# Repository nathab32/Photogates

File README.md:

# Photogate

[Video Demo](https://www.youtube.com/watch?v=dZhynI2hOx8)

## Description

Photogates allow precise, automatic timing of objects moving between two points. The photogates trigger automatically when a laser beam is interrupted, providing much faster response times than a human ever could with a stopwatch.

This specific project was inspired by my Science Olympiad team's lack of a photogate for the timing events. Commonly available solutions online cost at least $50, with high resolution ones costing hundreds of dollars. This design seeks to lower the barrier to precise timing by using commonly available parts and 3D printed materials for a cost-effective design. The design is fully open source to allow others to replicate and improve on it.

## Features

- Based on the Arduino UNO R3
- Swappable lasers and phototransistors
- Lasers and phototransistors mount to standard lab stands
- Displays last 3 recorded times
- Adjustable sensitivity
- Fully THT design
- Easy assembly

## Basic Usage

1. Position the two lasers perpendicular to the direction of travel at your specified distance.

2. Position the two phototransistors directly across from the two lasers. Each laser should hit straight onto a phototransistor.

3. Plug the lasers into the right side of the main module, and the phototransistors into the left side. The polarities are indicated on the silkscreen: a `+` for the lasers, and a `-` for the phototransistors.

4. When the module first powers on, calibration of the phototransistors will occur. The laser beams should be shining onto the phototransistors when this first occurs.

5. After calibration, make sure that the phototransistors are functioning by each beam independently. One of the interruptions should start the timing, indicated by `Timing...` on the LCD. The other interruption should stop the timing.
   - This is a good time to check the order of the phototransistors. If the order is incorrect, then simply plug the phototransistor in the top slot into the bottom slot and vice versa.

6. If everything has been executed correctly, then your photogate should be ready for timing! If you need to recalibrate at any point, simply press `R` again.

## Assembly

### 3D Printing

All 3D printing related files are included in the [`3D_Printing`](3D_Printing) directory. This includes the original `.f3d`, `.step`, and `.3mf` files.

If you don't use the `.3mf` file to slice, below are the parameters that I used.

|Parameter|Value|
|---------|-----|
|Material|PLA|
|Layer Height|0.2mm|
|Nozzle|0.4mm|
|Infill|<20%|

The biggest issue I had was with printing the lettering due to some elephant's foot, but if you have a multicolor printer then this won't be an issue. Otherwise, you may need to play around with the letter offsets and/or printer settings to get the letters to fit. The lettering is also entirely visual, so you can skip it if you want.

### Lasers

1. Cut and strip the 2 strand wire to the necessary length.

2. Cut heat shrink to the necessary length. I used heat shrink with a diameter that allows it to grab onto the laser diode's PCB when flattened so some strain relief is provided to the wire.

3. Solder female headers to one end of the wire.

4. Remove the presoldered wire from the laser diode, taking note of which side of the resistor the negative wire was attached to.

5. Slip the heat shrink onto the 2 strand wire.

6. Solder the 2 strand wire to the laser diode. The negative wire should bypass the included resistor by soldering to the side that the original wire wasn't connected to. Otherwise, the current source circuit may not be able to drive the laser.
    - A multimeter in the diode mode can check which side of the resistor to solder to. The side of the resistor with a lower voltage reading bypasses the resistor.

7. Test the connection by plugging the headers onto the laser pins on the shield and powering it on.

8. If laser powers on, then use the heat shrink over the flat portion of the laser's PCB. Don't slide it over the metal cylindrical section, otherwise the laser won't fit into the 3D printed mount.

9. Slide the laser diode into the 3D print, and use a M3x10 set screw to hold it in place.

10. Place the nut into the 3D print, and screw the eye bolt in. You can optionally glue the nut in place, but I chose not to just so I can remove it later if necessary.

The finshed result should look something like this:

### Phototransistors

1. Score and cut a 1x6 section of copper plated perfboard. If your perfboard has one continous copper side, then remove a small line of copper the middle of the board, leaving connections from holes 1-3 and holes 4-6.

2. Drill the first and last holes in the perfboard with a 7/64" drill bit to allow a M2 screw through.

3. Cut and strip the 2 strand wire to the necessary length.

4. Solder female headers to one end of the wire.

5. Bend the phototransistor leads towards the flat side of the package approximately 2.5mm from the bottom of the package. The phototransistor should be able to sit inside of the recession in the 3D print and the leads should stick through the 3rd and 4th holes of the perfboard.

6. With the phototransistor inside the recession, screw the perfboard to the 3D print using 2 M2x4 screws with the copper side facing out.

7. Solder the phototransistor to the perfboard, careful not to let the two sides short out.

8. Solder the 2 strand wire to the two remaining holes in the perfboard. With the phototransistor pointing down, the collector/positive is the right hole, and the emitter/negative is the left hole.

9. Test the connection by measuring the "resistance" of the phototransistor. With the positive lead connected to the collecter and negative lead connected to the emitter, the resistance should start high and go lower when exposed to light. When the leads are switched, the resistance is always high or open.

10. Place the nut into the 3D print, and screw the eye bolt in. You can optionally glue the nut in place, but I chose not to just so I can remove it later if necessary.

11. With a small strip of black electrical tape, cover the back side of the phototransistor to stop ambient light from hitting the sensor.

12. Glue the 3D printed cylinder to the mount, making sure that it sits perpendicular to the front face of the mount and doesn't interfere with the path of light.

The finshed result should look something like this:

### Shield

1. Order a PCB from your desired PCB manufacturer (I used JLCPCB) with the included [Gerbers](PCB/Gerber.zip). Refer to the following image for the ordering info: 

2. Using the included [KiCad project](PCB/KiCad.zip), solder the components to their respective places on the PCB. Everything is throughhole and can be soldered by hand, but be especially careful while soldering the transistors since the pitch is quite small. The schematics and PCB can also be viewed in [`photos/Circuit`](photos/Circuit).

### Final Assembly

1. Screw the Arduino UNO R3 onto the bottom plate with 4x M3x6 screws.

2. Firmly push the shield onto the top of the UNO, making sure that all header pins line up.

3. Place the top cover over the shield, and firmly push down until the cover snaps into place.

4. Glue the lettering and buttons into place.
   - Make sure not to test the fit for the buttons (with the cover on as well) before gluing. When gluing, make sure not to put too much that it clogs up the button.

5. Upload the code by cloning this repository and opening the folder in PlatformIO. Simply plug in the Arduino to your computer, go to [main.cpp](src/main.cpp), and hit the arrow in the top right corner (Ctrl+Alt+U) and wait for the success message.

6. Test that everything works by going to [Basic Usage](#basic-usage)

## BOM

The BOM can be viewed in [`BOM.csv`](BOM.csv)

## Todo

- distance input for avg speed
- switch phototransistor 0 and 1 (automatically?)
- single laser mode
- Output data to serial
- New board: control laser on/off with arduino

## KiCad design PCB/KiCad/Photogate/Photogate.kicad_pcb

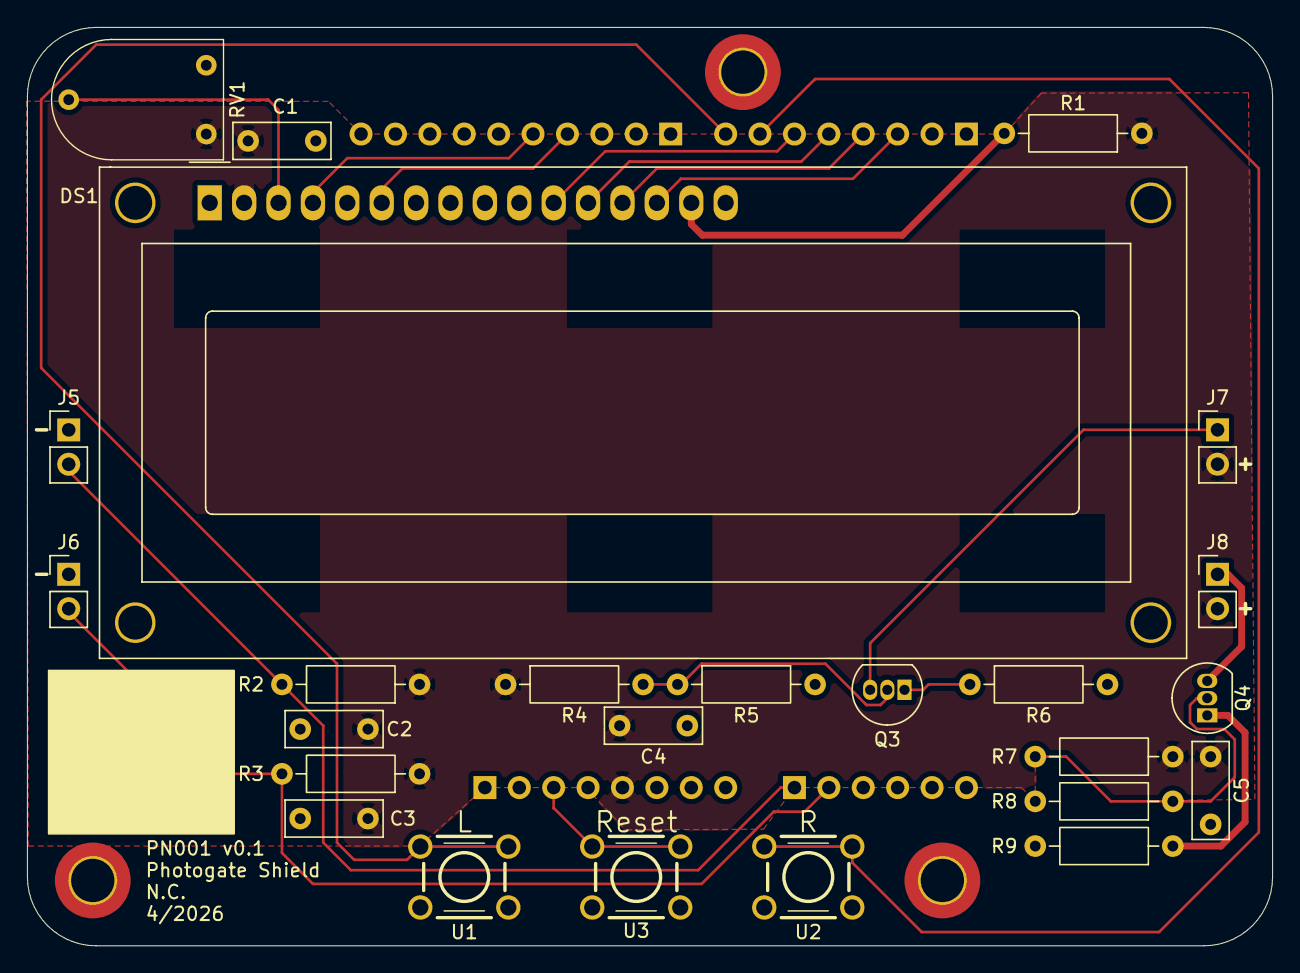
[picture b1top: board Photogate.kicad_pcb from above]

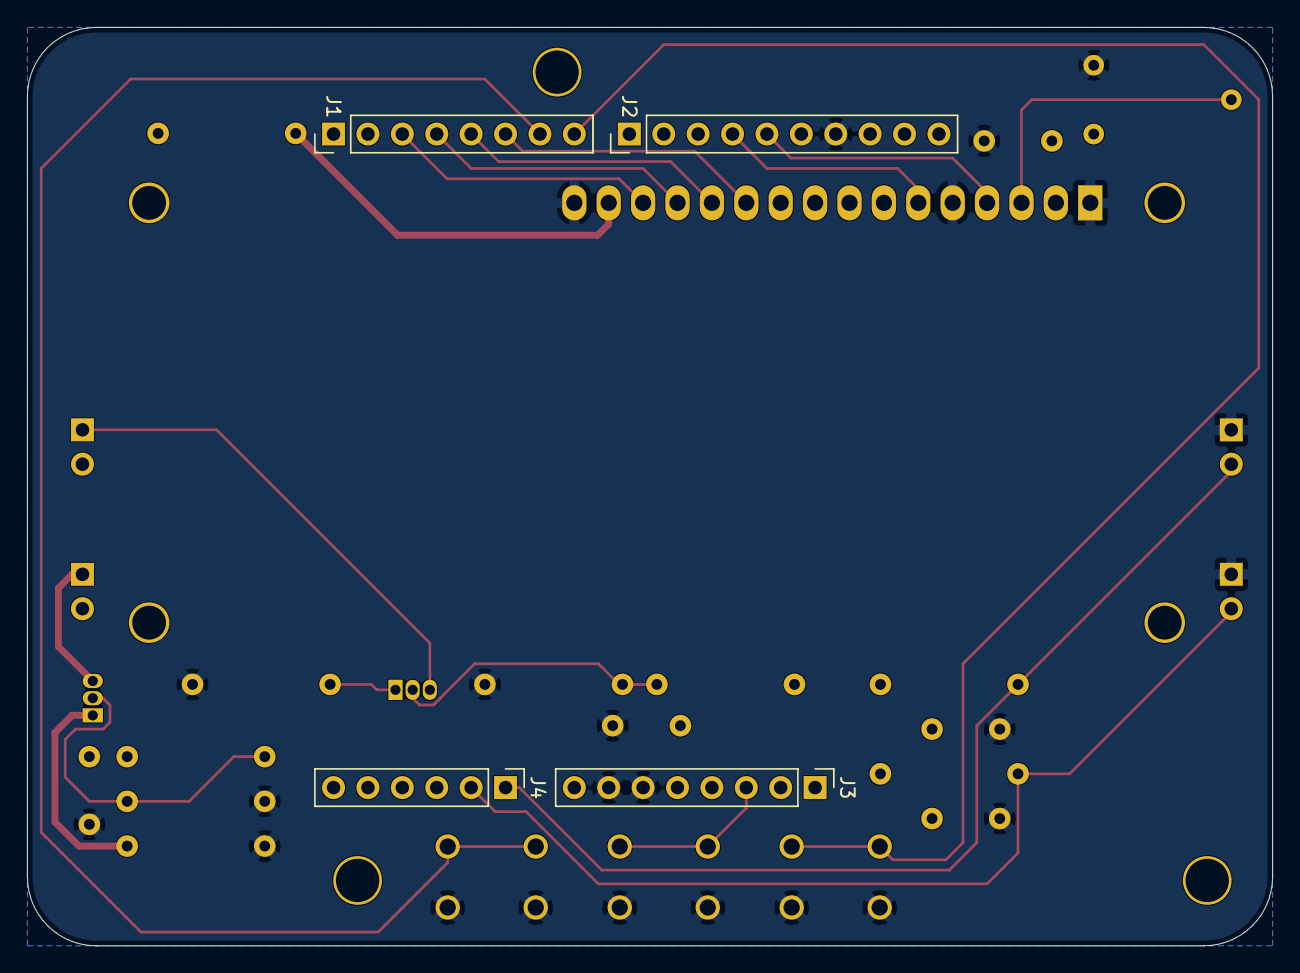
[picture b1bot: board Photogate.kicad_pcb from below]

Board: 2 copper layers, 91.9 x 67.8 mm, 29 parts (4 on the bottom side), 21 nets.

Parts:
C1: 1u; C_Rect_L7.0mm_W2.5mm_P5.00mm
C2, C3, C4, C5: 0.1u; C_Rect_L7.0mm_W2.5mm_P5.00mm
DS1: WC1602A
J1: Arduino_Digital_0_7; PinHeader_1x08_P2.54mm_Vertical
J2: Arduino_Digital_8_13; PinHeader_1x10_P2.54mm_Vertical
J3: Arduino_Power; PinHeader_1x08_P2.54mm_Vertical
J4: Arduino_Analog_IN; PinHeader_1x06_P2.54mm_Vertical
J5, J6, J7, J8: Conn_01x02_Pin; PinHeader_1x02_P2.54mm_Vertical
Q3, Q4: 2N3904; TO-92_Inline
R1: 220; R_Axial_DIN0207_L6.3mm_D2.5mm_P10.16mm_Horizontal
R2, R3: 100k; R_Axial_DIN0207_L6.3mm_D2.5mm_P10.16mm_Horizontal
R4, R5, R7, R8: 1k; R_Axial_DIN0207_L6.3mm_D2.5mm_P10.16mm_Horizontal
R6, R9: 100; R_Axial_DIN0207_L6.3mm_D2.5mm_P10.16mm_Horizontal
RV1: 10k; Bourns_3352E
U1, U2, U3: SPST-NO Switch; SW-TH_4P-L6.0-W6.0-P4.50-LS6.5

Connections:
+5V: C1.1, C2.1, C3.1, C4.1, C5.1, DS1.2 (VDD), J3.5, J7.2, J8.2, R1.1, R2.1, R3.1, R4.1, R7.1, RV1.3
/LCD/D4: DS1.11 (D4), J1.6
/LCD/D5: DS1.12 (D5), J1.5
/LCD/D6: DS1.13 (D6), J1.4
/LCD/D7: DS1.14 (D7), J1.3
/LCD/E: DS1.6 (E), J2.4
/LCD/RS: DS1.4 (RS), J2.5
/Phototransistor1/GATE_OUT_1: J4.1, J5.2, R2.2
/Phototransistor2/GATE_OUT_1: J4.2, J6.2, R3.2
GND: C1.2, C2.2, C3.2, C4.2, C5.2, DS1.1 (VSS), DS1.5 (R/W), DS1.16 (LED(-)), J2.7, J3.6, J3.7, J5.1, J6.1, R5.2, R6.2, R8.2, R9.2, RV1.1, U1.3, U1.4, U2.3, U2.4, U3.3, U3.4
unnamed: DS1.15 (LED(+)), R1.2
unnamed: DS1.3 (VO), RV1.2
unnamed: J1.7, U2.1, U2.2
unnamed: J1.8, U1.1, U1.2
unnamed: J3.3, U3.1, U3.2
unnamed: J7.1, Q3.3 (C)
unnamed: J8.1, Q4.3 (C)
unnamed: Q3.2 (B), R4.2, R5.1
unnamed: Q3.1 (E), R6.1
unnamed: Q4.2 (B), R7.2, R8.1
unnamed: Q4.1 (E), R9.1

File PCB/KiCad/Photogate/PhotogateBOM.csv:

#,Qty,Reference,Value,Description
1,1,A1,Arduino_UNO_R3,"Arduino UNO Microcontroller Module, release 3"
2,1,C1,1u,Unpolarized capacitor
3,4,"C2,C3,C4,C5",0.1u,Unpolarized capacitor
4,1,DS1,WC1602A,"LCD 16x2 Alphanumeric , 8 bit parallel bus, 5V VDD"
5,1,J1,Arduino_Digital_0_7,01x08 2.54mm Pin Headers
6,1,J2,Arduino_Digital_8_13,01x10 2.54mm Pin Headers
7,1,J3,Arduino_Power,01x08 2.54mm Pin Headers
8,1,J4,Arduino_Analog_IN,01x06 2.54mm Pin Headers
9,4,"J5,J6,J7,J8",Conn_01x02_Pin,01x02 2.54mm Pin Headers
10,2,"LD1,LD2",LASER-650NM,"Laser diode, cathode on pin 1, anode on pin 2"
11,2,"Q1,Q2",PT928-6C-F,"NPN phototransistor, collector/emitter"
12,2,"Q3,Q4",2N3904,"0.2A Ic, 40V Vce, Small Signal NPN Transistor, TO-92"
13,1,R1,220,Resistor
14,2,"R2,R3",100k,Resistor
15,4,"R4,R5,R7,R8",1k,Resistor
16,2,"R6,R9",100,Resistor
17,1,RV1,10k,Potentiometer
18,3,"U1,U2,U3",SPST-NO Switch,6mm x 6mm Tactile Switch

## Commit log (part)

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2026-04-10 Initial basic program
2026-04-13 Made phototransistors work by changing logic, and made output to LCD look nice
2026-04-23 Fixed issue with blocking code, while still fixing the issue of triggering over and over the photogate when both beams are interrupted. Also changed threshold to an int and only calculate when necess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
2026-04-29 Add readme with outline of sections, and basic usage completed
2026-04-29 Update readme with more text sections completed
2026-04-30 Add photos of laser and phototransistor examples
2026-04-30 Add images, finish text of assembly section
2026-04-30 test if images work now
2026-04-30 Fix rest of images
2026-05-02 Upload BOM
2026-05-02 Add .step files for the laser and phototransistor mounts
2026-05-02 remove extra column
2026-05-02 Add images of circuits/cad
2026-05-02 More improvements on readme, each section has stuff now
2026-05-07 Added step and fusion files for 3D printing
2026-05-07 Add render
2026-05-07 Add render image + improve shield section
2026-05-10 add extra costs
2026-05-10 Add magazine pdf + png
2026-05-10 Move images
2026-05-10 Reupload 3d printing files, add assembly + 3mf
2026-05-10 Add image of magazine, more specific about lettering
2026-05-12 Increase bottom text spacing
2026-05-12 Add kicad+manufacturing files
2026-05-12 Add PCB ordering instructions and related image to README
2026-05-12 Add KiCAD files
2026-05-12 Remove snapshots
2026-05-12 remove space
2026-05-12 fix links
2026-05-12 Update instructions for uploading code in README
2026-05-25 Move assembly file and add step assembly
2026-05-25 Add picture of PCB in cad
2026-06-02 Update threshold calculation
2026-06-02 Update readme to reflect calibration procedure
2026-06-02 change threshold calculation in resetSensitivity()
2026-06-02 images of built device
2026-06-02 rename and move images to new folder
2026-06-02 crop and rotate photo
2026-06-02 Upload updated magazine
2026-06-03 Add video demo to readme
